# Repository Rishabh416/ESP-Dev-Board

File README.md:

The ESP32 chip is the most versatile and easy to use chip in my opinion given its IoT functionality. 
I took on this project with the guide provided on the HackClub website to enhance my PCB skills as I have primarily only worked on simpler projects with less routing. 
This ESP dev board is unique since it has a male header allowing me to plug it directly into my PC rather than needing to stretch a cable for it.

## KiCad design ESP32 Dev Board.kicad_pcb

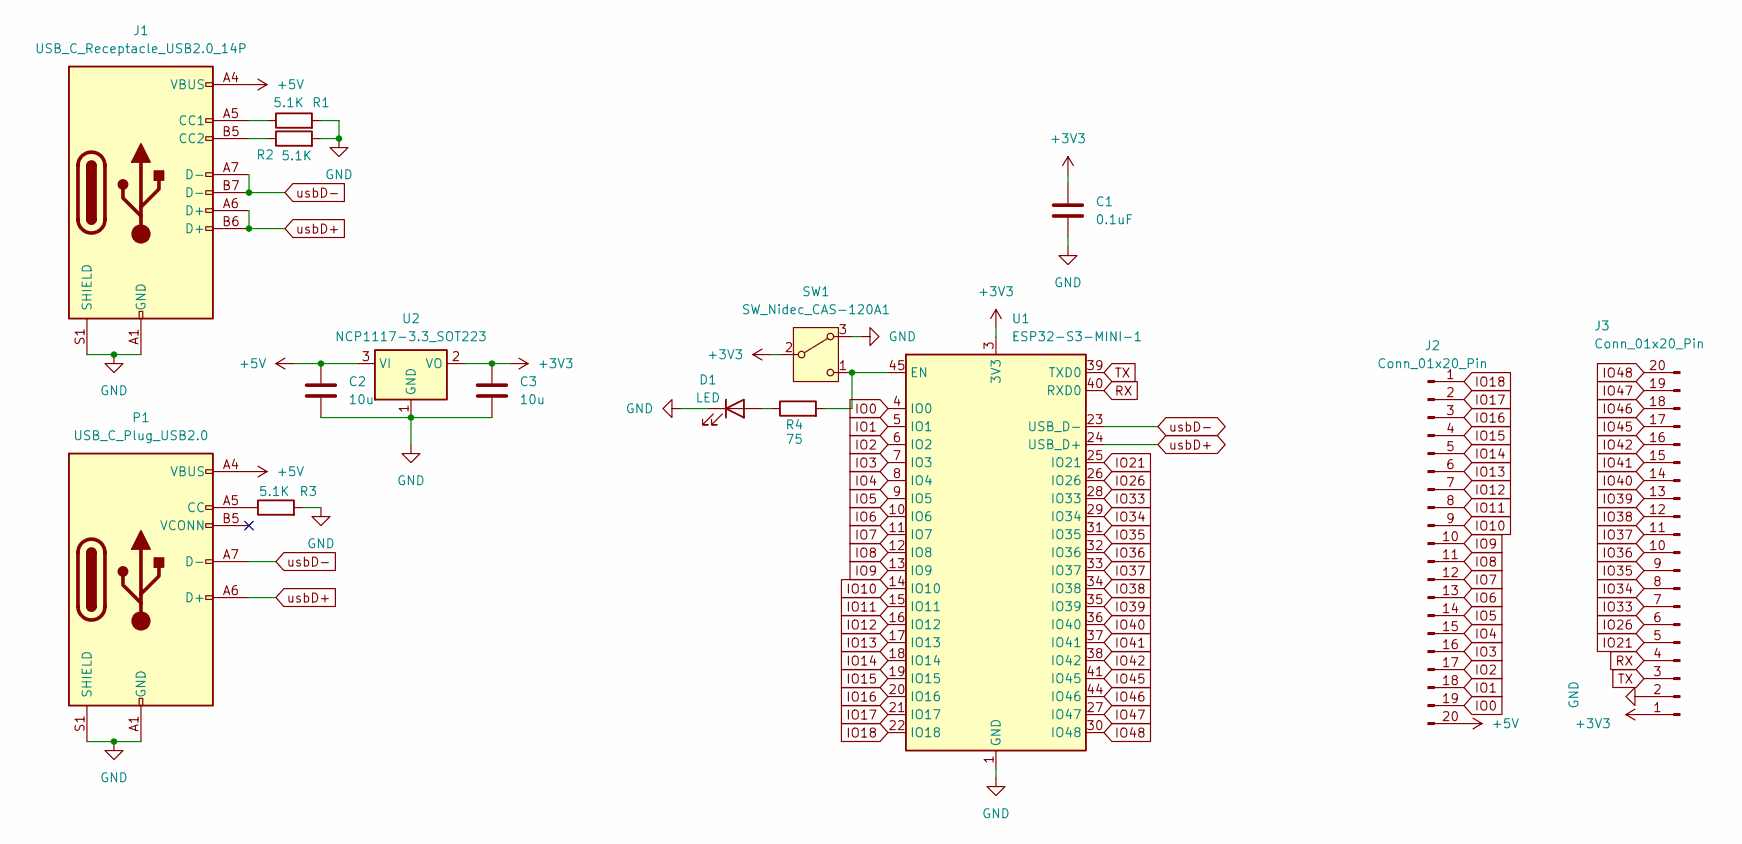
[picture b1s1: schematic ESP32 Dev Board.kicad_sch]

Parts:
C1: 0.1uF; C_0402_1005Metric
C2, C3: 10u; C_0603_1608Metric
D1: LED; LED_0402_1005Metric
J1: USB_C_Receptacle_USB2.0_14P; USB_C_Plug_Molex_105444
J2, J3: Conn_01x20_Pin; PinHeader_1x20_P2.54mm_Vertical
P1: USB_C_Plug_USB2.0; USB_C_Plug_Molex_105444
R1, R2, R3: 5.1K; R_0402_1005Metric
R4: 75; R_0402_1005Metric
SW1: SW_Nidec_CAS-120A1; Nidec_Copal_CAS-120A
U1: ESP32-S3-MINI-1; ESP32-S2-MINI-1
U2: NCP1117-3.3_SOT223; SOT-223-3_TabPin2

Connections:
+3V3: C1.1, C3.1, J3.1, SW1.2 (B), U1.3 (3V3), U2.2 (VO)
+5V: C2.1, J1.A4 (VBUS), J1.A9 (VBUS), J1.B4 (VBUS), J1.B9 (VBUS), J2.20, P1.A4 (VBUS), P1.A9 (VBUS), P1.B4 (VBUS), P1.B9 (VBUS), U2.3 (VI)
GND: C1.2, C2.2, C3.2, D1.1 (K), J1.A1 (GND), J1.A12 (GND), J1.B1 (GND), J1.B12 (GND), J1.S1 (SHIELD), J3.2, P1.A1 (GND), P1.A12 (GND), P1.B1 (GND), P1.B12 (GND), P1.S1 (SHIELD), R1.2, R2.2, R3.2, SW1.3 (A), U1.1 (GND), U1.2 (GND), U1.42 (GND), U1.43 (GND), U1.46 (GND), U1.47 (GND), U1.48 (GND), U1.49 (GND), U1.50 (GND), U1.51 (GND), U1.52 (GND), U1.53 (GND), U1.54 (GND), U1.55 (GND), U1.56 (GND), U1.57 (GND), U1.58 (GND), U1.59 (GND), U1.60 (GND), U1.61 (GND), U1.62 (GND), U1.63 (GND), U1.64 (GND), U1.65 (GND), U2.1 (GND)
IO0: J2.19, U1.4 (IO0)
IO1: J2.18, U1.5 (IO1)
IO2: J2.17, U1.6 (IO2)
IO3: J2.16, U1.7 (IO3)
IO4: J2.15, U1.8 (IO4)
IO5: J2.14, U1.9 (IO5)
IO6: J2.13, U1.10 (IO6)
IO7: J2.12, U1.11 (IO7)
IO8: J2.11, U1.12 (IO8)
IO9: J2.10, U1.13 (IO9)
IO10: J2.9, U1.14 (IO10)
IO11: J2.8, U1.15 (IO11)
IO12: J2.7, U1.16 (IO12)
IO13: J2.6, U1.17 (IO13)
IO14: J2.5, U1.18 (IO14)
IO15: J2.4, U1.19 (IO15)
IO16: J2.3, U1.20 (IO16)
IO17: J2.2, U1.21 (IO17)
IO18: J2.1, U1.22 (IO18)
IO21: J3.5, U1.25 (IO21)
IO26: J3.6, U1.26 (IO26)
IO33: J3.7, U1.28 (IO33)
IO34: J3.8, U1.29 (IO34)
IO35: J3.9, U1.31 (IO35)
IO36: J3.10, U1.32 (IO36)
IO37: J3.11, U1.33 (IO37)
IO38: J3.12, U1.34 (IO38)
IO39: J3.13, U1.35 (IO39)
IO40: J3.14, U1.36 (IO40)
IO41: J3.15, U1.37 (IO41)
IO42: J3.16, U1.38 (IO42)
IO45: J3.17, U1.41 (IO45)
IO46: J3.18, U1.44 (IO46)
IO47: J3.19, U1.27 (IO47)
IO48: J3.20, U1.30 (IO48)
unnamed: D1.2 (A), R4.1
unnamed: J1.A5 (CC1), R1.1
unnamed: J1.B5 (CC2), R2.1
unnamed: P1.A5 (CC), R3.1
unnamed: R4.2, SW1.1 (C), U1.45 (EN)
RX: J3.4, U1.40 (RXD0)
TX: J3.3, U1.39 (TXD0)
usbD+: J1.A6 (D+), J1.B6 (D+), P1.A6 (D+), U1.24 (USB_D+)
usbD-: J1.A7 (D-), J1.B7 (D-), P1.A7 (D-), U1.23 (USB_D-)

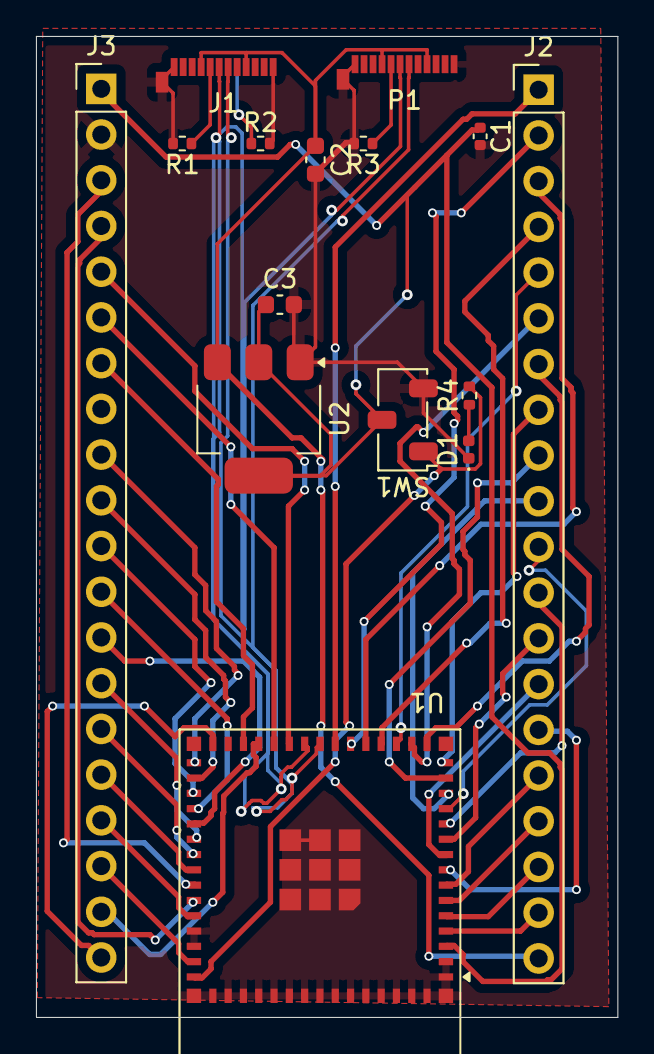
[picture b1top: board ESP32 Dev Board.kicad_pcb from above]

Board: 2 copper layers, 32.3 x 54.5 mm, 15 parts (0 on the bottom side), 47 nets.

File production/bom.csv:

Designator,Footprint,Quantity,Value,LCSC Part #
C1,0402,1,0.1uF,
"C2, C3",0603,2,10u,
D1,0402,1,LED,
J1,USB_C_Plug_Molex_105444,1,USB_C_Receptacle_USB2.0_14P,
"J2, J3",PinHeader_1x20_P2.54mm_Vertical,2,Conn_01x20_Pin,
P1,USB_C_Plug_Molex_105444,1,USB_C_Plug_USB2.0,
"R1, R2, R3",0402,3,5.1K,
R4,0402,1,75,
SW1,Nidec_Copal_CAS-120A,1,SW_Nidec_CAS-120A1,
U1,ESP32-S2-MINI-1,1,ESP32-S3-MINI-1,
U2,SOT-223-3_TabPin2,1,NCP1117-3.3_SOT223,

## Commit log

2026-06-22 added production files
